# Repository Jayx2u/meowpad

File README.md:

# MeowPad
I love cats. You better love cats. Here's a macropad with addressable RGB, hot-swappable switches and an acrylic case to stare at the beautiful cat silkscreen art. Cats my beloved. Cats forever.
## Renders

## PCB

## KiCad Designs

## Case
_Hackpad YSWS Note: Whilst this is an acrylic case and not for 3D printing, I have access to acrylic sheets and a laser cutter so I'm able to supply the case myself. Also able to supply all the screws, o-rings and nuts._

## BOM
| Component                             | Quantity |
|---------------------------------------|----------|
| Seeed Studio XIAO RP2040              | 1        |
| Keycaps                               | 9        |
| Cherry MX Switches                    | 9        |
| Cherry Kailh Sockets                  | 9        |
| 1N4148W (SOD123)                      | 9        |
| 500ohm THT Resistor                   | 1        |
| WS2812B                               | 6        |

## Acknowledgement
- MX Cherry switches symbol, footprint and model from [sszczep/kicad-libraries/](https://github.com/sszczep/kicad-libraries/tree/master)
- Cute cats from [Neko Atsume](https://www.nekoatsume.com/en/)

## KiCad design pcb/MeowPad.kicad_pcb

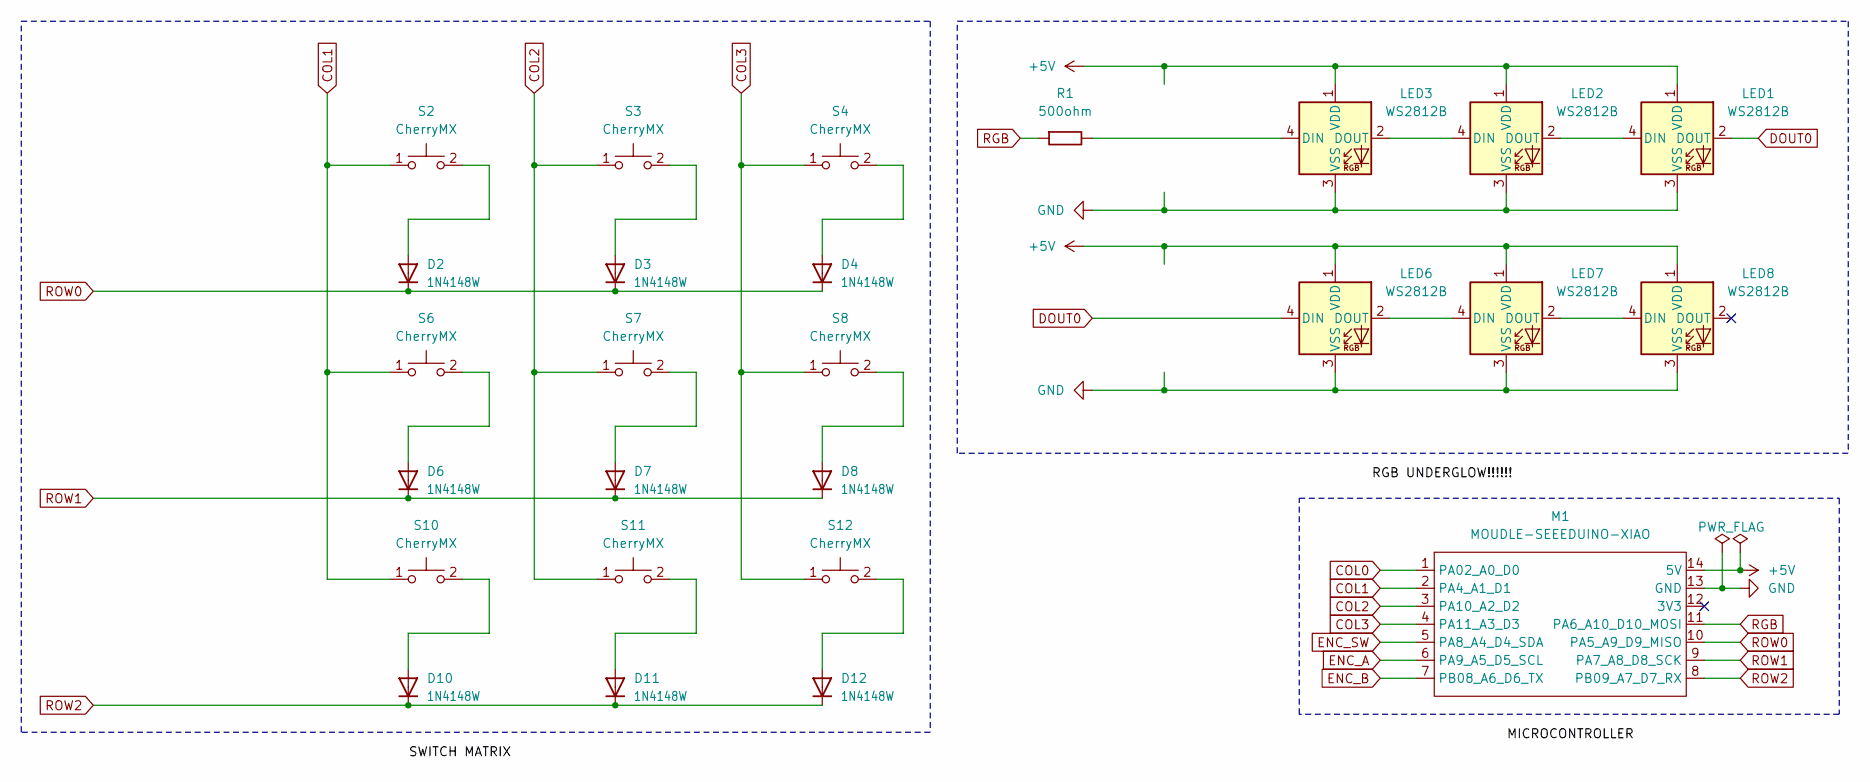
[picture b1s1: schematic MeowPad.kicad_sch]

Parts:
D2, D3, D4, D6, D7, D8, D10, D11, D12: 1N4148W; MICROBUILDER_SOD-123
LED1, LED2, LED3, LED6, LED7, LED8: WS2812B; LED_WS2812B_PLCC4_5.0x5.0mm_P3.2mm
M1: MOUDLE-SEEEDUINO-XIAO; MOUDLE14P-SMD-2.54-21X17.8MM
R1: 500ohm; R_Axial_DIN0207_L6.3mm_D2.5mm_P10.16mm_Horizontal
S2, S3, S4, S6, S7, S8, S10, S11, S12: CherryMX; CherryMX_1.00u_KailhSocket

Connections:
+5V: LED1.1 (VDD), LED2.1 (VDD), LED3.1 (VDD), LED6.1 (VDD), LED7.1 (VDD), LED8.1 (VDD), M1.14 (5V)
COL0: M1.1 (PA02_A0_D0)
COL1: M1.2 (PA4_A1_D1), S2.1, S6.1, S10.1
COL2: M1.3 (PA10_A2_D2), S3.1, S7.1, S11.1
COL3: M1.4 (PA11_A3_D3), S4.1, S8.1, S12.1
DOUT0: LED1.2 (DOUT), LED6.4 (DIN)
ENC_A: M1.6 (PA9_A5_D5_SCL)
ENC_B: M1.7 (PB08_A6_D6_TX)
ENC_SW: M1.5 (PA8_A4_D4_SDA)
GND: LED1.3 (VSS), LED2.3 (VSS), LED3.3 (VSS), LED6.3 (VSS), LED7.3 (VSS), LED8.3 (VSS), M1.13 (GND)
unnamed: D2.A, S2.2
unnamed: D3.A, S3.2
unnamed: D4.A, S4.2
unnamed: D6.A, S6.2
unnamed: D7.A, S7.2
unnamed: D8.A, S8.2
unnamed: D10.A, S10.2
unnamed: D11.A, S11.2
unnamed: D12.A, S12.2
unnamed: LED1.4 (DIN), LED2.2 (DOUT)
unnamed: LED2.4 (DIN), LED3.2 (DOUT)
unnamed: LED3.4 (DIN), R1.2
unnamed: LED6.2 (DOUT), LED7.4 (DIN)
unnamed: LED7.2 (DOUT), LED8.4 (DIN)
RGB: M1.11 (PA6_A10_D10_MOSI), R1.1
ROW0: D2.C, D3.C, D4.C, M1.10 (PA5_A9_D9_MISO)
ROW1: D6.C, D7.C, D8.C, M1.9 (PA7_A8_D8_SCK)
ROW2: D10.C, D11.C, D12.C, M1.8 (PB09_A7_D7_RX)

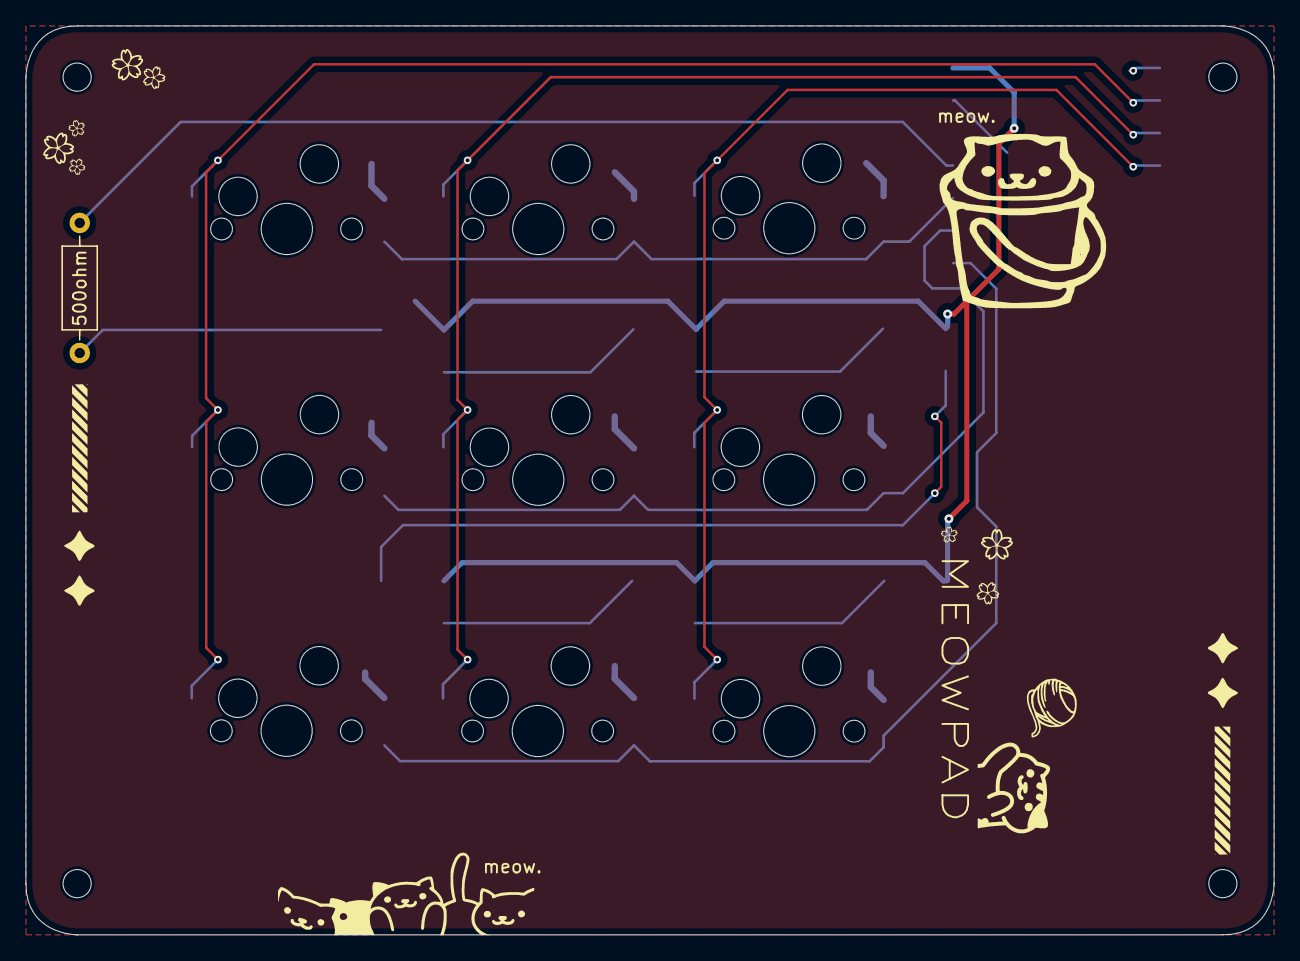
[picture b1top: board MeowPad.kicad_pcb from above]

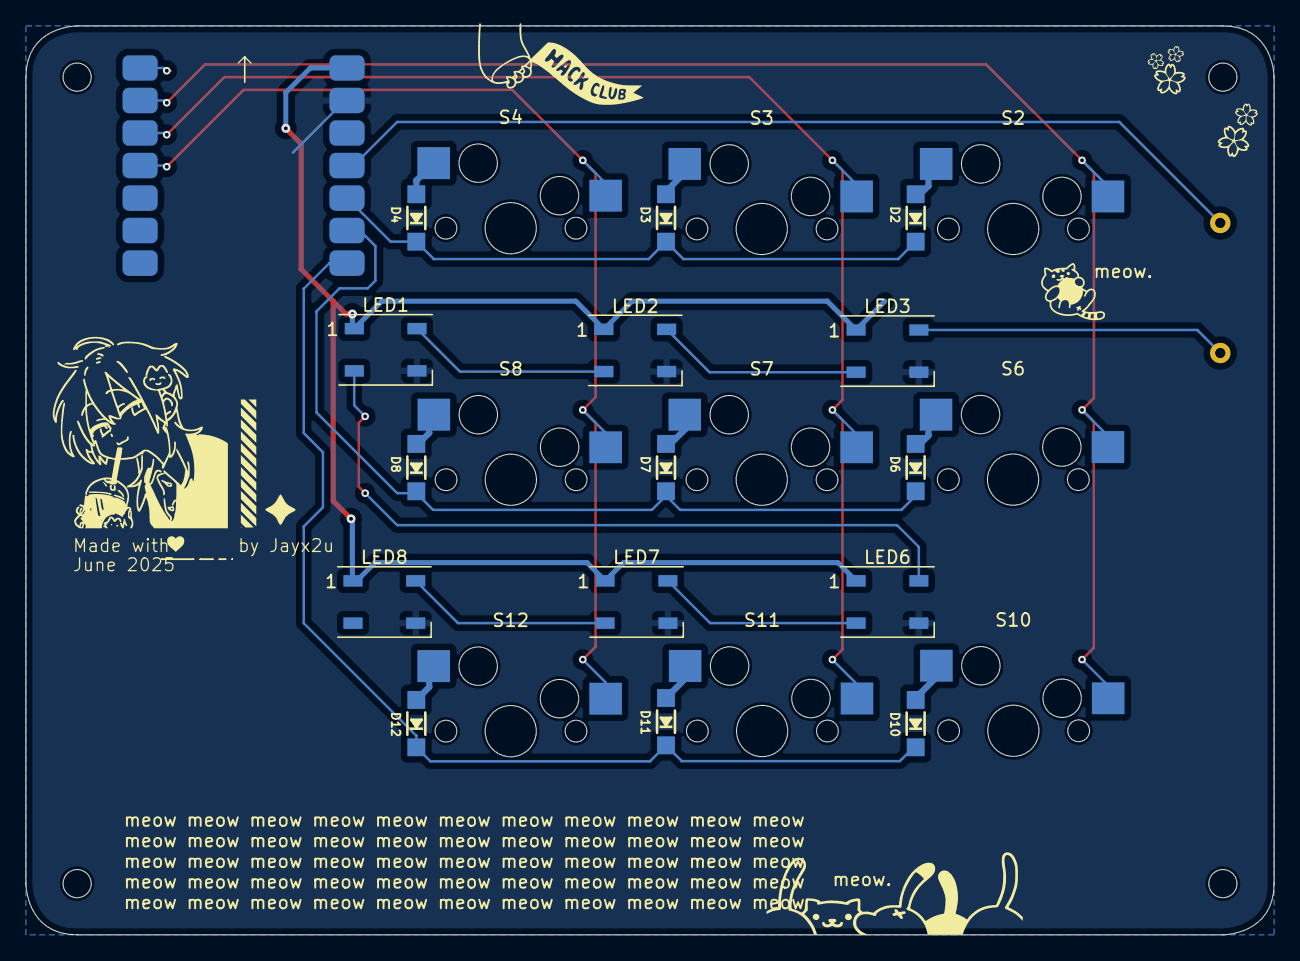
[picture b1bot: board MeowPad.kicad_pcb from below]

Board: 2 copper layers, 97.5 x 71.0 mm, 26 parts (16 on the bottom side), 24 nets.

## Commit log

2025-06-24 Upload PCB
2025-06-24 Add production files
2025-06-24 Add firmware
2025-06-24 Update PCB
2025-06-24 Add assets
2025-06-24 Add render
2025-06-24 Add more photos
2025-06-24 Add BOM
2025-06-24 Update BOM
2025-06-25 Add case files
